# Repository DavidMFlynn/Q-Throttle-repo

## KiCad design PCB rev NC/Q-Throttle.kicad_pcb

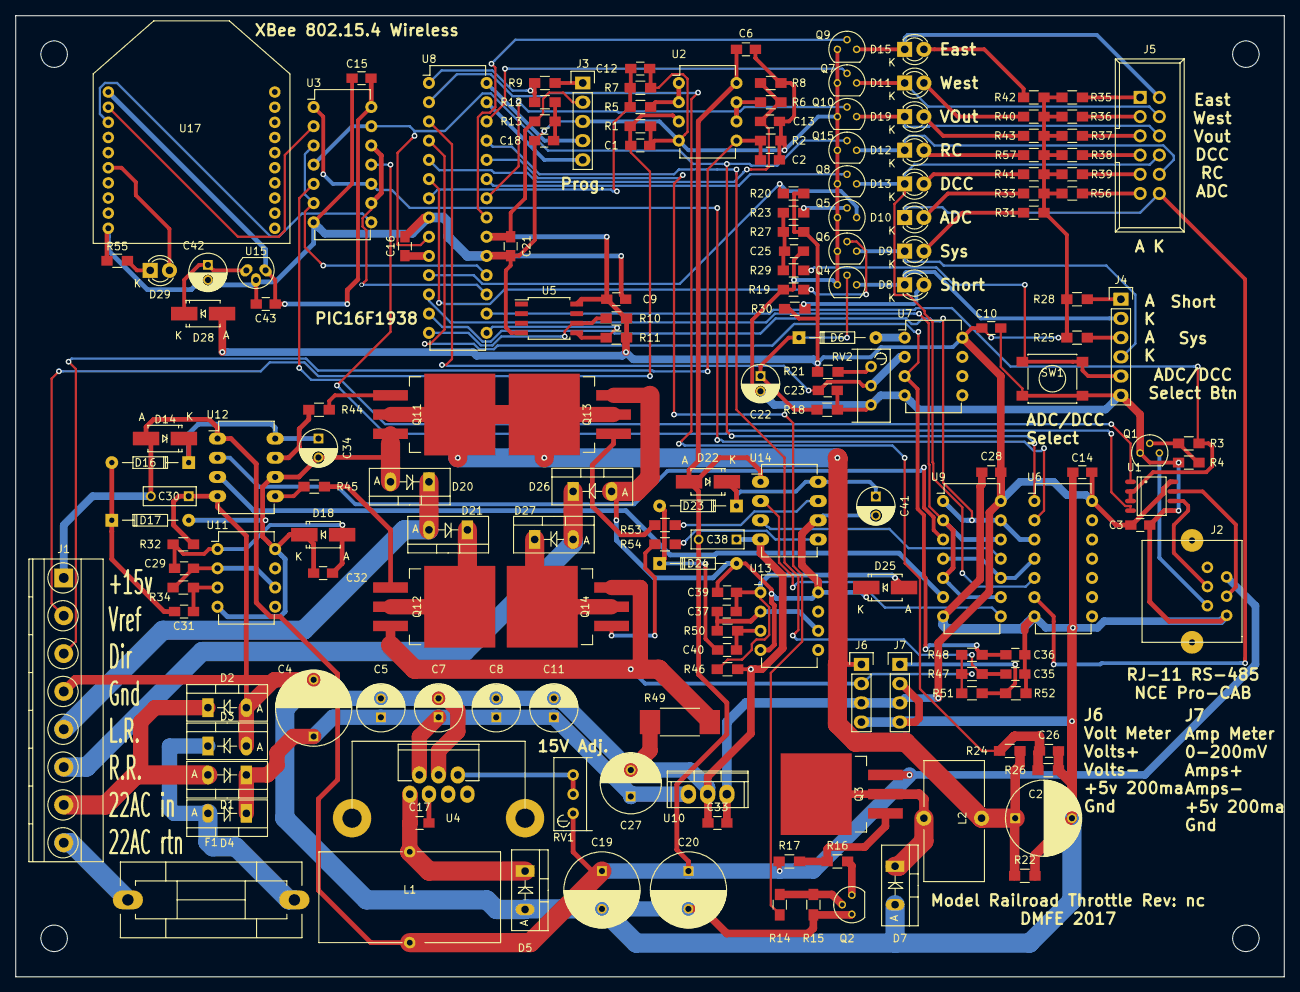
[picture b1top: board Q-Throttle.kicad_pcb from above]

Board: 2 copper layers, 167.6 x 127.0 mm, 177 parts (0 on the bottom side), 120 nets.

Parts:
C1, C2, C3, C6, C9, C10, C12, C13, C14, C15, C16, C18, C21, C23, C25, C26, C28, C32, C33, C35, C36, C39: 0.1uf; C_0805_HandSoldering
C4: 1000uF 50v; C_Radial_D10_L20_P7.5
C5, C7, C8: 15uF 50v; C_Radial_D6.3_L11.2_P2.5
C11: 0.47uF 50v; C_Radial_D6.3_L11.2_P2.5
C17, C31, C40: 0.01uf; C_0805_HandSoldering
C19, C20: 220uF 50v; C_Radial_D10_L13_P5
C22: 2.2uF 25v; C_Radial_D5_L11_P2
C24: 1000uF 25v; C_Radial_D10_L20_P7.5
C27: 100uf 50v; C_Radial_D8_L11.5_P3.5
C29, C37: 0.001uf; C_0805_HandSoldering
C30, C38: 1uf poly; C_Rect_L7_W2.5_P5
C34, C41: 6.8uF 35v Tant; C_Radial_D5_L6_P2.5
C42: 2.2uf 25V; C_Radial_D5_L11_P2
C43: 0.1 uf; C_0805_HandSoldering
D1, D2, D3, D4, D5, D7, D20, D21, D26, D27: SBL845; Diode_TO-220_Vertical
D6, D16, D17, D23, D24: 1N4148; Diode_DO-35_SOD27_Horizontal_RM10
D8, D9, D10, D11, D12, D13, D15, D19, D29: LED; LED-3MM
D14, D22: B140 Fast; SMA_Handsoldering
D18, D25: SMA 15V; SMA_Handsoldering
D28: 1N4007; SMA_Handsoldering
F1: FUSE; Fuseholder5x20_horiz_SemiClosed_Casing10x25mm
H1, H2, H3, H4: MountingHole_3-5mm
J1: CONN_01X08; TerminalBlock_Pheonix_MKDS1.5-8pol
J2: RJ-11; RJ12_E
J3: CONN_01X05; Pin_Header_Straight_1x05
J4: CONN_01X06; Pin_Header_Straight_1x06
J5: CONN_01X12; IDC_Header_Straight_12pins
J6, J7: CONN_01X04; Pin_Header_Straight_1x04
L1: 33uH; Choke_Toroid_12x24mm_Vertical
L2: 100uH; Choke_Toroid_8x16mm_Vertical
Q1, Q2, Q4, Q5, Q6, Q7, Q8, Q9, Q10, Q15: 2N7000; TO-92_Molded_Narrow
Q3: Q_PMOS_GDS; TO-263-3Lead
Q11, Q12, Q13, Q14: N-Ch TO-263; TO-263-3Lead
R1, R2: 4.7M; R_0805_HandSoldering
R3, R44, R45, R53, R54: 47Ω; R_0805_HandSoldering
R4, R5, R6, R10, R11, R15, R17, R20, R23, R24, R27, R47, R48: 10K; R_0805_HandSoldering
R7, R8, R13, R21: 4.7K; R_0805_HandSoldering
R9: 100Ω; R_0805_HandSoldering
R12, R14, R16, R25, R28, R29, R31, R33, R35, R36, R37, R38, R39, R40, R41, R42, R43, R56, R57: 1K; R_0805_HandSoldering
R18, R19, R34, R50: 100K; R_0805_HandSoldering
R22: 1.5K; R_0805_HandSoldering
R26: 2.2K; R_0805_HandSoldering
R30: 470Ω; R_0805_HandSoldering
R32, R46: 10Ω; R_0805_HandSoldering
R49: 0.1Ω; R_2512_HandSoldering
R51: 10.0K; R_0805_HandSoldering
R52: 1.00K; R_0805_HandSoldering
R55: 200Ω; R_0805_HandSoldering
RV1: 5KΩ; Potentiometer_Bourns_3296W_3-8Zoll_Inline_ScrewUp
RV2: 1KΩ; Potentiometer_Bourns_3296W_3-8Zoll_Inline_ScrewUp
SW1: SW_PUSH; SW_SPST_PTS645
U1: SP3485CN; SO-8
U2: LM6132A; DIP-8_W7.62mm
U3: 74LS125_(3V3); DIP-14_W7.62mm
U4: LM2677-12; TO-220-7C_w_heatsink
U5: MB85RC256V; SOIJ-8_5.3x5.3mm_Pitch1.27mm
U6: 74HCT04; DIP-14_W7.62mm
U7: LM358; DIP-8_W7.62mm
U8: PIC16(L)F1938-I/SP; DIP-28_W7.62mm
U9: 74LS08; DIP-14_W7.62mm
U10: LM7805CT; TO-220
U11, U13: LM555CN; DIP-8_W7.62mm
U12, U14: IR2102; DIP-8_W7.62mm_LongPads
U15: LM78Lxx; TO-92_Molded_Narrow_Oval
U17: XBee_S1; XBee

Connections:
+3V3: C15.1, C43.1, U3.14, U15.1, U17.1
+5V: C3.1, C9.1, C10.1, C14.1, C21.1, C28.2, C33.2, D28.2, J3.2, J6.3, J7.3, R10.1, R11.1, R13.1, R20.1, R21.1, R25.2, R27.1, R28.2, R30.1, R31.1, R33.2, R35.2, R36.2, R37.2, R38.2, R39.2, R40.2, R41.2, R42.2, R43.2, R56.2, R57.2, U1.8, U5.8, U6.14, U7.8, U8.20, U9.14, U10.3
+15V: C6.1, C19.1, C20.1, C30.2, C38.2, D14.2, D22.2, J1.1, J2.2, L1.2, Q3.3, R17.1, RV1.1, U2.8, U12.1, U14.1
+24V: C4.1, C5.1, C7.1, C8.1, C11.1, C27.1, D1.1, D4.1, U4.2, U10.1
DCC: Q8.2, U8.23
DRV: U6.3, U8.13, U9.1, U9.13
DRVENA: U8.12, U9.2, U9.5, U9.9, U9.12
East: Q9.2, U8.21
GND: C1.2, C2.2, C3.2, C4.2, C5.2, C6.2, C7.2, C8.2, C9.2, C10.2, C11.2, C12.2, C13.2, C14.2, C15.2, C16.1, C18.2, C19.2, C20.2, C21.2, C22.2, C23.2, C24.2, C25.2, C26.2, C27.2, C28.1, C30.1, C33.1, C35.1, C36.1, C38.1, C42.2, C43.2, D2.2, D3.2, D5.2, D7.2, J1.4, J2.6, J3.3, J4.6, J6.4, J7.2, J7.4, Q1.1, Q2.1, Q4.1, Q5.1, Q6.1, Q7.1, Q8.1, Q9.1, Q10.1, Q15.1, R1.2, R2.2, R4.2, R7.2, R8.2, R15.2, R18.2, R19.2, R22.2, R26.2, R32.2, R46.2, R49.2, R52.2, R55.2, RV2.3, SW1.2, U1.5, U2.4, U3.7, U4.4, U5.4, U6.7, U7.4, U8.8, U8.19, U9.7, U10.2, U12.4, U14.4, U15.2, U17.10
IFB: C35.2, R47.2, U8.25
ITRIP+: C36.2, R48.2, U7.3, U8.4
LeftRail: D20.1, D21.2, J1.5
M+: C24.1, J6.1, L2.2, Q11.2, Q13.2, R22.1, R24.2
unnamed: C1.1, J1.2, R1.1, U2.3
unnamed: C2.1, J1.3, R2.1, U2.5
unnamed: C12.1, R5.1, R7.1, U8.7
unnamed: C13.1, R6.1, R8.1, U8.5
unnamed: C16.2, U8.10
unnamed: C17.1, D5.1, L1.1, U4.1
unnamed: C17.2, U4.3
unnamed: C18.1, R12.1, R13.2
unnamed: C22.1, D6.1, Q4.2, R18.1
unnamed: C23.1, RV2.2, U7.2, U8.3
unnamed: C25.1, R23.1, R27.2, R29.2
unnamed: C26.1, R24.1, R26.1, U8.2
unnamed: C29.1, C32.1, D18.2, R32.1, U11.1
unnamed: C29.2, R34.2, U11.2, U11.6
unnamed: C31.1, D16.2, D17.1
unnamed: C31.2, R34.1, U11.3
unnamed: C32.2, C34.2, D17.2, D18.1, D20.2, Q11.3, U11.4, U11.8, U12.6
unnamed: C34.1, D14.1, D16.1, U12.8
unnamed: C37.1, C39.1, D25.2, R46.1, U13.1
unnamed: C37.2, R50.2, U13.2, U13.6
unnamed: C39.2, C41.2, D24.2, D25.1, D26.2, Q13.3, U13.4, U13.8, U14.6
unnamed: C40.1, D23.2, D24.1
unnamed: C40.2, R50.1, U13.3
unnamed: C41.1, D22.1, D23.1, U14.8
unnamed: C42.1, D28.1, U15.3
unnamed: D1.2, D2.1, J1.7
unnamed: D3.1, D4.2, F1.2
unnamed: D6.2, U7.1
unnamed: D7.1, L2.1, Q3.2
unnamed: D8.1, J4.2, Q4.3
unnamed: D8.2, R30.2
unnamed: D9.1, J4.4, Q6.3
unnamed: D9.2, R31.2
unnamed: D10.1, J5.12, U6.6
unnamed: D10.2, R33.1
unnamed: D11.1, J5.4, Q7.3
unnamed: D11.2, R40.1
unnamed: D12.1, J5.10, Q15.3
unnamed: D12.2, R57.1
unnamed: D13.1, J5.8, Q8.3, U6.5
unnamed: D13.2, R41.1
unnamed: D15.1, J5.2, Q9.3
unnamed: D15.2, R42.1
unnamed: D19.1, J5.6, Q10.3
unnamed: D19.2, R43.1
unnamed: D21.1, Q12.2
unnamed: D27.1, Q14.2
unnamed: D29.1, R55.1
unnamed: D29.2, U17.6
unnamed: F1.1, J1.8
unnamed: J2.3, U1.6
unnamed: J2.4, U1.7
unnamed: J2.5, Q1.3
unnamed: J3.1, R9.2
unnamed: J3.4, U8.28
unnamed: J3.5, U8.27
unnamed: J4.1, R28.1
unnamed: J4.3, R25.1
unnamed: J4.5, R29.1, SW1.1
unnamed: J5.1, R35.1
unnamed: J5.3, R36.1
unnamed: J5.5, R37.1
unnamed: J5.7, R38.1
unnamed: J5.9, R39.1
unnamed: J5.11, R56.1
unnamed: J6.2, Q12.3, Q14.3, R47.1, R48.1, R49.1, R51.2
unnamed: J7.1, R51.1, R52.1
unnamed: Q1.2, R3.1, R4.1
unnamed: Q2.2, R14.1, R15.1
unnamed: Q2.3, R16.2
unnamed: Q3.1, R16.1, R17.2
unnamed: Q5.2, R23.2
unnamed: Q5.3, R20.2, U8.11
unnamed: Q6.2, R19.1, U8.6
unnamed: Q11.1, R44.2
unnamed: Q12.1, R45.1
unnamed: Q13.1, R53.2
unnamed: Q14.1, R54.1
unnamed: R3.2, U1.2, U1.3, U8.16
unnamed: R5.2, U2.1, U2.2
unnamed: R6.2, U2.6, U2.7
unnamed: R10.2, U5.6, U8.14
unnamed: R11.2, U5.5, U8.15
unnamed: R9.1, R12.2, U8.1
unnamed: R14.2, U8.24
unnamed: R21.2, RV2.1
unnamed: R44.1, U12.7
unnamed: R45.2, U12.5
unnamed: R53.1, U14.7
unnamed: R54.2, U14.5
unnamed: RV1.2, RV1.3, U4.6
unnamed: U1.1, U3.5
unnamed: U1.4, U3.11
unnamed: U3.1, U3.10, U6.2
unnamed: U3.3, U3.6, U8.18
unnamed: U3.9, U3.12, U8.17
unnamed: U6.4, U9.4, U9.10
unnamed: U9.3, U12.2
unnamed: U9.6, U12.3
unnamed: U9.8, U14.2
unnamed: U9.11, U14.3
RCmode: Q15.2, U3.4, U3.13, U6.1, U8.9
RightRail: D26.1, D27.2, J1.6
Vout: Q10.2, U8.22
West: Q7.2, U8.26
XB_Din: U3.8, U17.3
XB_Dout: U3.2, U17.2

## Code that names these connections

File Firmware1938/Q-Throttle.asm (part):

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;   Pin 6  RA4/T0CKI		RA4, SysLED (Active High)
;   Pin 7  RA5/AN4		AN4, VRef Input from DMFE handheld
;   Pin 8  Vss	GND
;   Pin 9  RA7/OSC1		RA7, RCMode Serial select (0=RS-485, 1=X-BEE)
;   Pin 10 RA6/OSC2	VCAP
;   Pin 11 RC0		ADC/DCC Select Switch (Active High)
;   Pin 12 RC1/CCP2		mosfet Drive enable/PWM
;   Pin 13 RC2/CCP1		mosfet Drive East/West select
;   Pin 14 RC3		SCL I2C RAM
;
;   Pin 15 RC4		SDA I2C RAM
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;   Pin 18 RC7/RX		RS-232 RX
;   Pin 19 Vss	GND
;   Pin 20 Vdd	+5V
;   Pin 21 RB0/AN12		East LED (Active High)
;   Pin 22 RB1/AN10		VOut LED (Active High)
;   Pin 23 RB2/AN8		DCC/ADC* LED (Active High)
;   Pin 24 RB3/AN9/CCP2	VOUTPWM
;   Pin 25 RB4/AN11		AN11 IFB Track Current
;   Pin 26 RB5/AN13		West LED (Active High)
;   Pin 27 RB6/ICSPCLK		ICSPCLK
;   Pin 28 RB7/ICSPDAT		ICSPDAT
;
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PortBDDRBits	EQU	b'11010000'	;outputs
PortBValue	EQU	b'11000011'
;
#Define	EastLED	LATB,0	;East LED (Active High)
#Define	VOutLED	LATB,1	;VOut LED (Active High)
#Define	DCCLED	LATB,2	;DCC/ADC* LED (Active High)
;			;RB3=CCP2 VOUTPWM
;			;RB4=AN11 IFB Track Current
#Define	WestLED	LATB,5	;West LED (Active High)
;			;RB6=ICSPCLK
;			;RB7=ICSPDAT
;
PortCDDRBits	EQU	b'11111001'
PortCValue	EQU	b'00000000'
;
#Define	SW1_Btn	PORTC,0	;ADC/DCC Select Switch (Active High)
#Define	DRVENA	LATC,1	;mosfet Drive enable/PWM
#Define	DRV_Dir	LATC,2	;mosfet Drive East/West* select
#Define	RC3_In	PORTC,3	;SCL I2C RAM
#Define	RC4_In	PORTC,4	;SDA I2C RAM
#Define	RS485Send	PORTC,5	;RS-485 Send/Recieve*
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
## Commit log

2017-11-30 Updated Rev A PCB
2018-09-30 begin coding
2018-10-01 led fix
2018-11-01 analog
